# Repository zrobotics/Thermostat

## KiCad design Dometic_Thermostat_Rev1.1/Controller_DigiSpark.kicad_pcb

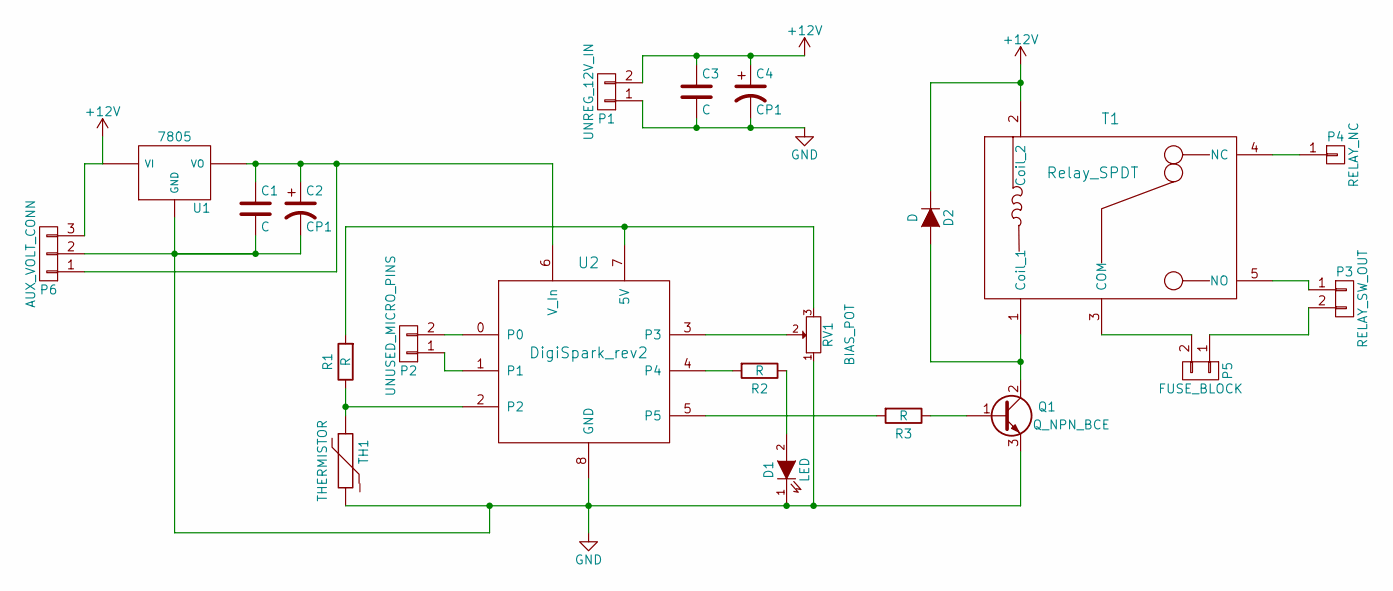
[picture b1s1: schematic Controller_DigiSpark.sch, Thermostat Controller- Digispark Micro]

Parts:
C1, C3: C; C_Disc_D4.3mm_W1.9mm_P5.00mm
C2, C4: CP1; CP_Radial_D14.0mm_P5.00mm
D1: LED; LED_D3.0mm
D2: D; D_5W_P12.70mm_Horizontal
P1: UNREG_12V_IN; SolderWirePad_2x_1-5mmDrill-CUSTOM
P2: UNUSED_MICRO_PINS; Pin_Header_Straight_1x02_Pitch2.00mm
P3: RELAY_SW_OUT; SolderWirePad_2x_1-5mmDrill-CUSTOM
P4: RELAY_NC; SolderWirePad_single_1-5mmDrill
P5: FUSE_BLOCK; Fuse_Block_Blade
P6: AUX_VOLT_CONN; Pin_Header_Straight_1x03_Pitch2.54mm
Q1: Q_NPN_BCE; TO-220_Horizontal
R1, R2, R3: R; R_Axial_DIN0309_L9.0mm_D3.2mm_P12.70mm_Horizontal
RV1: BIAS_POT; POT_3310P
T1: Relay_SPDT; RLY_JSM1-12V-5
TH1: THERMISTOR; SolderWirePad_2x_1-5mmDrill-CUSTOMWIDE
U1: 7805; TO-220_78XX_REGULATOR
U2: DigiSpark_rev2; DIGISPARK_REV2

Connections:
+12V: C3.1, C4.1, D2.1 (K), P1.2, P6.3, T1.2 (Coil_2), U1.VI
GND: C1.2, C2.2, C3.2, C4.2, D1.1 (K), P1.1, P6.2, Q1.3 (E), RV1.1, TH1.2, U1.GND, U2.8 (GND)
unnamed: C1.1, C2.1, P6.1, U1.VO, U2.6 (V_In)
unnamed: D1.2 (A), R2.1
unnamed: D2.2 (A), Q1.2 (C), T1.1 (Coil_1)
unnamed: P2.1, U2.1
unnamed: P2.2, U2.0
unnamed: P3.1, T1.5 (NO)
unnamed: P3.2, P5.1
unnamed: P4.1, T1.4 (NC)
unnamed: P5.2, T1.3 (COM)
unnamed: Q1.1 (B), R3.1
unnamed: R1.1, TH1.1, U2.2
unnamed: R1.2, RV1.3, U2.7 (5V)
unnamed: R2.2, U2.4
unnamed: R3.2, U2.5
unnamed: RV1.2, U2.3

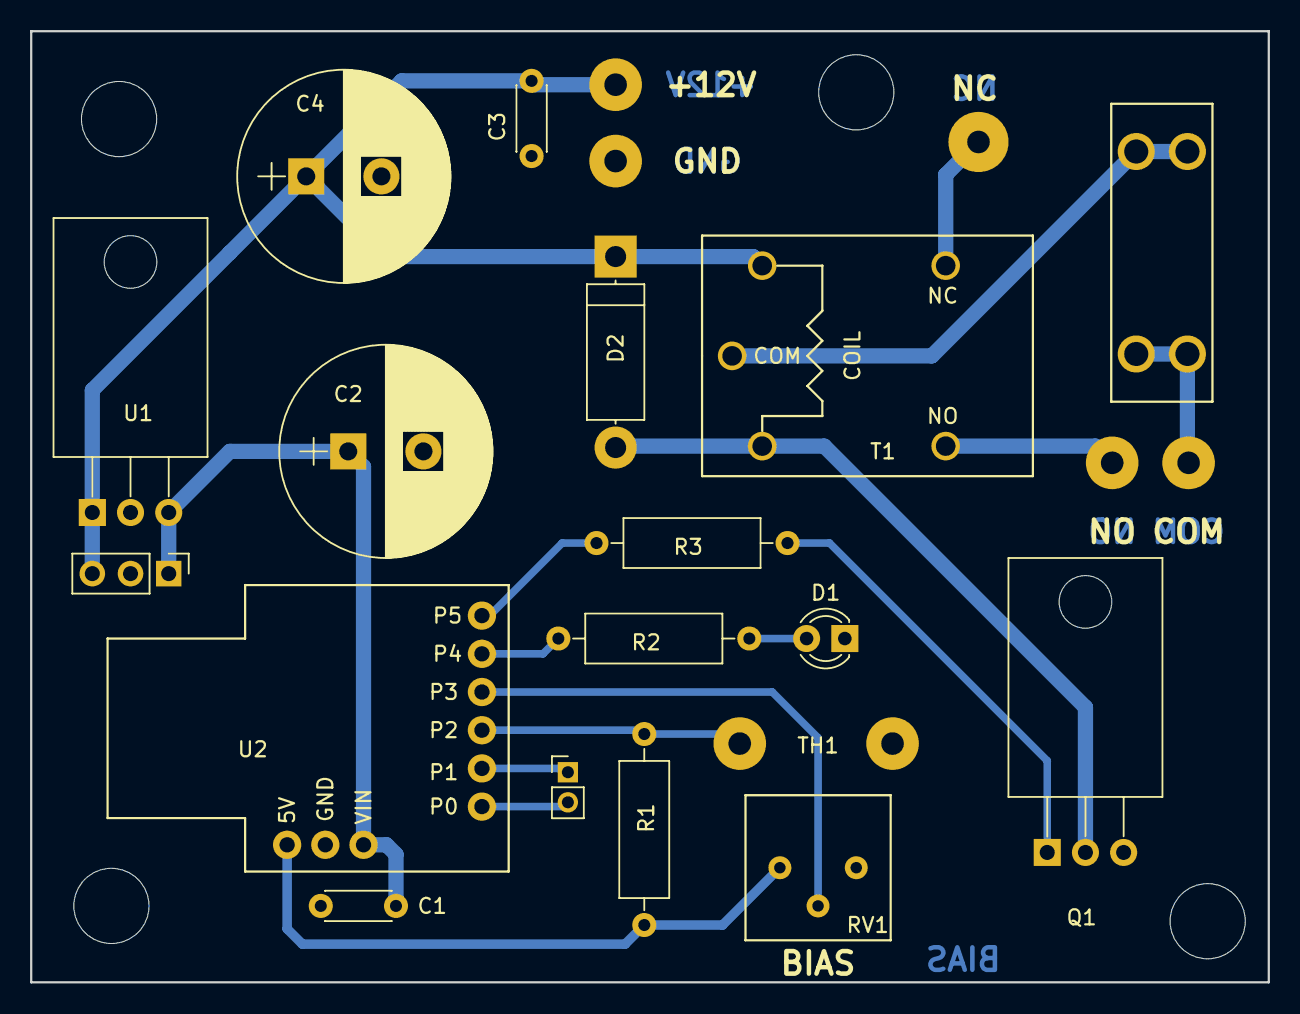
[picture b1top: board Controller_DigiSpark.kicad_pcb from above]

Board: 2 copper layers, 82.3 x 63.2 mm, 21 parts (0 on the bottom side), 17 nets.

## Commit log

2017-04-26 Removed BOM file exclusion
2017-04-26 Added first rev of board
2017-04-27 Added 1.3 rev, all progress up-to-date
2017-04-27 Added R4 in || w/ thermistor, value not calculated
    Changed thermistor config to series-parallel, increase linearity.
    Method detailed at:
    http://www.edn.com/design/sensors/4429105/Linearize-thermistors-with-new-formula
2017-04-27 Add R4, change footprints TH1 & LED
    Added R4 to board, changed thermistor and LED footprints.
2017-04-27 Changed some delay timings in firmware
2017-04-27 Cleaned up firmware logic
2017-04-27 Added test points, provided access to P4
    to directly tie LED to relay, cut trace b/w TP2 & TP3.
    Jump TP2 to TP1, then TP3 provides access to P4 of micro.
    This also cleaned up the ground plane around R2&3
2017-04-27 Added logo to B Cu
2017-05-14 Changed Schematic-updated relay driver to mosfet
2017-05-14 Schematic- changed pin assignment, changed darlington to mosfet
2017-05-14 Changed PCB-updated pin assg & added mount holes
2018-02-03 Included external files from digispark
2018-02-18 Changed delay timings, prevent hysterisis
    Added longer delay before changing relay state, relay cycling too much
    when state changed
